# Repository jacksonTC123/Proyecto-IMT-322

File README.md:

# Control Háptico para Drones con MPU6050

Proyecto que permite controlar un dron mediante movimientos de la mano, utilizando un sensor **MPU6050** que es un acelerómetro y giroscopio integrado en una PCB personalizada junto a una ESP-32 y un script en Python que recibe los datos por comunicacion serial del ESP-32 para enviar instrucciones de vuelo.

## Características principales
- **Control por movimientos**: Inclina tu mano para dirigir el dron.
- **PCB personalizada**: Diseño optimizado para el sensor MPU6050.
- **Software en Python**: Procesamiento de datos y comunicación con el dron.
- **Bajo costo**: Hardware accesible y código abierto.

## Hardware
### Componentes
- Sensor MPU6050 PCB personalizada
- Microcontrolador ESP32
- controlador de Dron con comunicacion Wifi
- Fuente de alimentación Batería LiPo 3.7V

### Diagrama de conexión
```plaintext
MPU6050 (PCB) → Microcontrolador → Python (PC) → WIFI → Dron

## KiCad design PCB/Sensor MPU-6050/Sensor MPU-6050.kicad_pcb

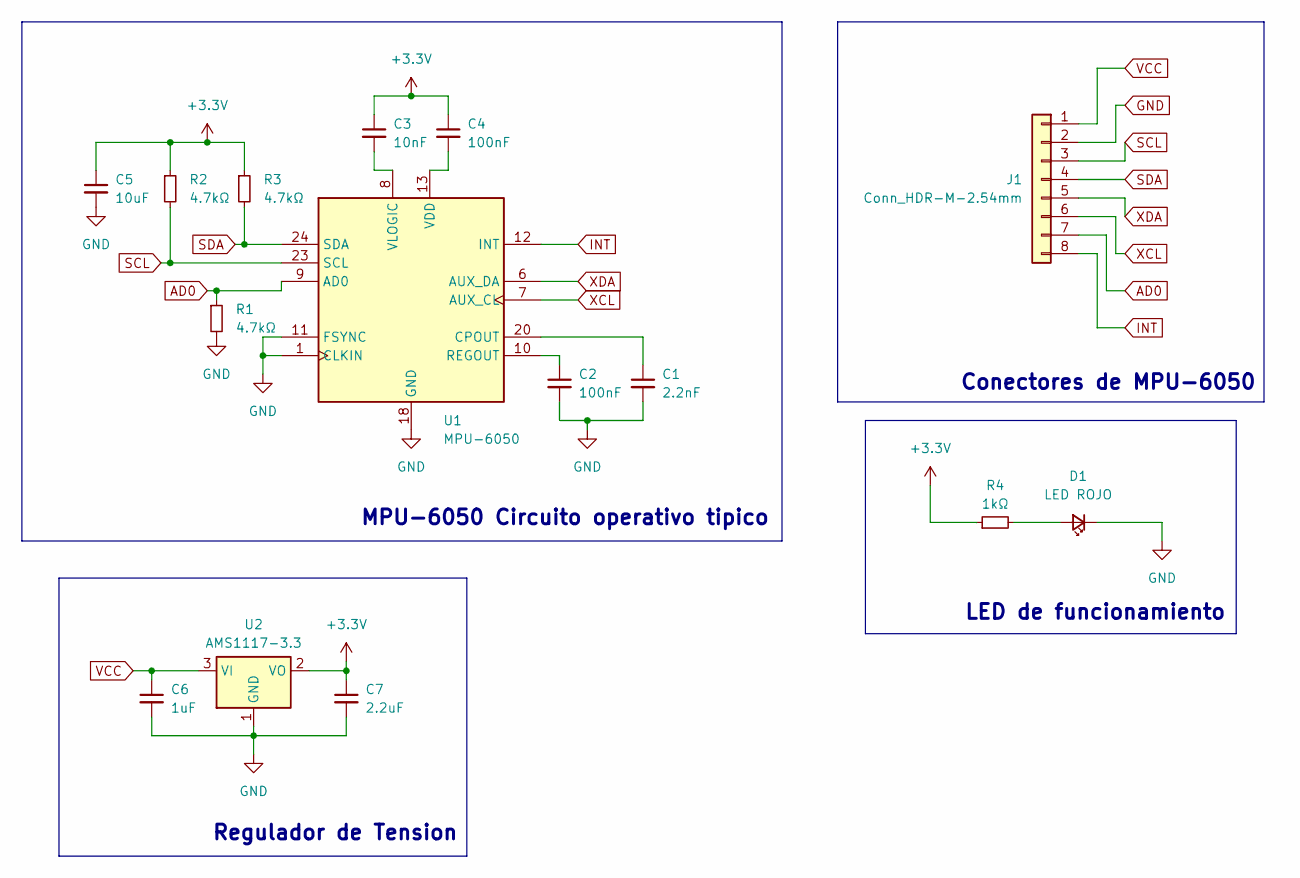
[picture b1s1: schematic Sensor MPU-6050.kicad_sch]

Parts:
C1: 2.2nF; C_0402_1005Metric
C2, C4: 100nF; C_0402_1005Metric
C3: 10nF; C_0402_1005Metric
C5: 10uF; C_0805_2012Metric
C6: 1uF; C_0603_1608Metric
C7: 2.2uF; C_0603_1608Metric
D1: LED ROJO; LED_0603_1608Metric
J1: Conn_HDR-M-2.54mm; PinHeader_1x08_P2.54mm_Vertical
R1, R2, R3: 4.7kΩ; R_0402_1005Metric
R4: 1kΩ; R_0603_1608Metric
U1: MPU-6050; QFN50P400X400X95-24N
U2: AMS1117-3.3; SOT-23-3

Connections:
+3.3V: C3.1, C4.1, C5.1, C7.1, R2.1, R3.1, R4.1, U2.2 (VO)
AD0: J1.7, R1.1, U1.9 (AD0)
GND: C1.2, C2.2, C5.2, C6.2, C7.2, D1.1 (K), J1.2, R1.2, U1.1 (CLKIN), U1.11 (FSYNC), U1.18 (GND), U2.1 (GND)
INT: J1.8, U1.12 (INT)
unnamed: D1.2 (A), R4.2
unnamed: C1.1, U1.20 (CPOUT)
unnamed: C2.1, U1.10 (REGOUT)
unnamed: C4.2, U1.13 (VDD)
unnamed: C3.2, U1.8 (VLOGIC)
SCL: J1.3, R2.2, U1.23 (SCL)
SDA: J1.4, R3.2, U1.24 (SDA)
VCC: C6.1, J1.1, U2.3 (VI)
XCL: J1.6, U1.7 (AUX_CL)
XDA: J1.5, U1.6 (AUX_DA)

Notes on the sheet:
Conectores de MPU-6050
LED de funcionamiento
Regulador de Tension
MPU-6050 Circuito operativo tipico

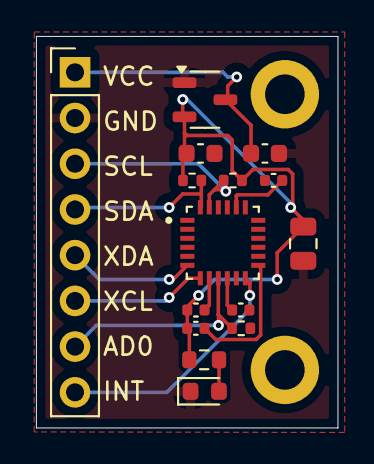
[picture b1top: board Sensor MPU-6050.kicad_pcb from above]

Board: 2 copper layers, 16.8 x 21.8 mm, 15 parts (0 on the bottom side), 14 nets.

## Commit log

2025-03-27 Creacion de rama y carpeta de Contenido
2025-06-05 #commit inicial
2025-06-05 MPU6050 funcionamiento
2025-06-12 Codigo control de Vuelo
2025-06-12 Actualizacion Codigo MPU6050
2025-06-12 actualizacion README.md
    Descripcion del proyecto
2025-06-12 Actualizacion en develop codigo MPU6050
2025-06-12 PCB MPU6050
2025-06-12 acttualizacion develop
2025-06-12 actualizacion codigo del dron
2025-06-12 actualizacion
2025-06-12 actualizacion final develop
2025-06-12 version de proyecto final
2025-06-12 version final
